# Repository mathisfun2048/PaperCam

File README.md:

# PaperCam: My Thought Process Behind This Project

## Description and Exigence

This is my third attempt at hardware design, and it's been so much fun!

The concept arose when I came across ads for disposable cameras for summer camps on YouTube. I remembered the nostalgia of taking instant pictures and the intrinsic joy they bring, but within the context of instant cameras being 1) expensive and 2) harmful to the environment. I want to bridge this gap by creating a digital camera that feels like an instant camera. 

The first thing I think of with instant photography is not knowing exactly how the picture is going to turn out; rather, just taking it and hoping for the best. That's why instead of opting for an LCD display, I chose an E-Ink display. Not only does it use significantly less power, but it can also show an instant snapshot *after* taking the picture, mimicking the feeling of instant photography. 

Another goal I had for this project was to intentionally keep things minimalistic. In a world where technology can have so many features, I wanted to create something simple with one purpose: taking a picture. There's this one Japanese brand (Muji!) that I have been enthralled with for the past 7 years, mainly due to their product's simplicity. Keeping this in mind, I was very mindful of which parts I needed to use. The only user inputs, really, are a power switch and a capture button, nothing excessive but enough to take a picture. Moreover, the e-ink display shows a glimpse of the photo after it has been taken, not necessarily the most detailed, but accurate enough to capture the likeness of whatever is being captured. I hope that this camera will encourage me to try to create memories instead of the best "picture" I hope this camera will let me be less preoccupied with how things look but rather will force me to capture things authentically. 

Here is everything I sourced. A identical version can be found in the BOM tab at the bottom of the README. 

NOTE: I know some items can be found cheaper through other retailars: the only problem is that my parents will only let me buy from the retailors below. If the cost goes above the allocated cost for my project, I will hapilly pay out of my own pocket. I am grateful to have the opportunity to build this, and I cannot do so if I don't buy the parts from the retailors below. 

| item                                       | quantity | cost   | source      | link                                                                                                                                                                                                             |
| ------------------------------------------ | -------- | ------ | ----------- | ---------------------------------------------------------------------------------------------------------------------------------------------------------------------------------------------------------------- |
| Raspberry Pi Zero 2 W                      | 1        | 14.99  | microcenter | [https://www.microcenter.com/product/643085/raspberry-pi-zero-2-w](https://www.microcenter.com/product/643085/raspberry-pi-zero-2-w)                                                                             |
| Camera                                     | 1        | 29.25  | adafruit    | [https://www.adafruit.com/product/5657](https://www.adafruit.com/product/5657)                                                                                                                                   |
| e-ink display                              | 1        | 34.99  | amazon      | [https://www.amazon.com/dp/B074NR1SW2](https://www.amazon.com/dp/B074NR1SW2)                                                                                                                                     |
| 64gb SD Card                               | 1        | 0      | myself      | n/a                                                                                                                                                                                                              |
| LiPo Batter 2200mAh                        | 1        | 9.95   | adafruit    | [https://www.adafruit.com/product/1781](https://www.adafruit.com/product/1781)                                                                                                                                   |
| powerboost 1000c                           | 1        | 19.95  | adafruit    | [https://www.adafruit.com/product/2465?srsltid=AfmBOop7pYqBCCEfueczVoFC1WawLn-4JDxrWe6MvBLNL__PzA9LbI22](https://www.adafruit.com/product/2465?srsltid=AfmBOop7pYqBCCEfueczVoFC1WawLn-4JDxrWe6MvBLNL__PzA9LbI22) |
| SPDT Switch                                | 1        | 0.95   | adafruit    | [https://www.adafruit.com/product/805](https://www.adafruit.com/product/805)                                                                                                                                     |
| 12mm Button                                | 1        | 5.95   | adafruit    | [https://www.adafruit.com/product/1010](https://www.adafruit.com/product/1010)                                                                                                                                   |
| Header for RPi                             | 1        | 1.75   | adafruit    | [https://www.adafruit.com/product/3907](https://www.adafruit.com/product/3907)                                                                                                                                   |
| 0.1uF Ceramic Capacitor                    | 2        | 1.95   | adafruit    | [https://www.adafruit.com/product/753](https://www.adafruit.com/product/753)                                                                                                                                     |
| 220uF Electrolytic Capacitor               | 1        | 2.95   | adafruit    | [https://www.adafruit.com/product/2192](https://www.adafruit.com/product/2192)                                                                                                                                   |
| Screws M2.5 × 6 mm \* 5, M2.5 x 10 mm \* 4 | 9        | 16.95  | adafruit    | [https://www.adafruit.com/product/3299](https://www.adafruit.com/product/3299)                                                                                                                                   |
| Custom PCB                                 | 1        | 8.6    | JCLPCB      | [https://jlcpcb.com](https://jlcpcb.com/)                                                                                                                                                                        |
| Total Cost                                 |          | ~148 |

## Schematic and PCB Design

I saw that with this project, spending all this time curating the BOM allowed my schematic and PCB design process to be significantly smoother. I was able to organically decide where components go such that the product can fulfill its purpose without having anything excess. I feel this starked my approach in my Hackpad design, where I flooded the PCB with an LED matrix, OLED, and encoder when perhaps the keys would have sufficed. The design of this project has been meditative, and I am grateful for that. One way I referenced this creative meditation in the design itself is through the inclusion of graphic design motifs I designed during the pandemic. The graphic design kept me sane then through its meditative nature, and I wanted to reference that simple creativity in the silkscreen. I will say that the silkscreen aesthetic starks the clean minimalistic nature of the CAD, and that is intentional: my graphic design motifs, in all their chaos, are a part of me and do not necessarily need to be advertised. To the user, I want the product to be simple elegant, and perfect for capturing memories. 

### Schematic

### PCB on Kicad

## Firmware

After I designed the PCB, I started on the firmware, the design of which garnered me the most personal growth. While I was able to exercise my research and design skills to a significantly larger extent in this project compared to Hackpad or Gamepad, the software designed for this is something I have never done before. I have never had multiple software files interact with each other in a product before. For instance, I started this project initially with just a runtime firmware, but then realized I needed to use shell too to initiate my code and the file structure and use the system to restart my Python code should it crash. I spent quite a bit coding, but I saw myself getting faster at it which amazed me. I started learning how to code maybe 2 years ago, and I am really proud of what I've been able to do here. 

Everything associated with the firmware can be found in the firmware directory. It has its own specialized README that explains what each file does. 

## CAD

After I was done with the code, I saved the hardest for last: CAD. I've never been good at CAD, but this project allowed me to show my style. When I did graphic design, I specialized in minimalistic designs which were meant to be abstract and aesthetically pleasing. I was highly influenced by the Bauhaus movement, and I am so glad I was able to incorporate that part of my personal style into this project. In keeping line with the "minimal" mindset, I wanted the design to be a simplified square Instax. That's why on the exterior form it almost looks like a kid's toy-- that is intentional. I don't want anything to distract from my camera being used to capture memories, even if it looks a tad blocky (I personally think it looks pretty cool). Making it look seamless on the outside was not easy, though. I utilized a top-case, bottom-case design where my PCB will screw into the bottom case before the top case is applied and the whole thing is screwed together. This required me to be able to hide my mounting screws inside the structure--the inside is much more chaotic than the clean exterior. For stability, I chose to indent the inside a tad so that the top case slides on and has a sense of rigidity. This is enhanced by the view-finder which acts as a "pole" holding everything together. I wanted my camera to not feel like something inherently precious, but rather something that can be taken places and used as a camera to capture memories. The only real adoration I have for it is the phrase "PaperCAM v1" on the user side of it. I want to remind myself that when I use this, it is something that I built and not something I simply bought. I want to remind myself that I have the agency to create things. 

Because everything is on a PCB this time, no fun illustrated wiring diagram :(. However, I did annotate the bellow images for y'all! 

## BOM

NOTE: I know some items can be found cheaper through other retailars: the only problem is that my parents will only let me buy from the retailors below. If the cost goes above teh allocated cost for my project, I will hapilly pay out of my own pocket. I am grateful to have the opportunity to build this, and I cannot do so if I don't buy the parts from the retailors below. 

| item                                       | quantity | cost   | source      | link                                                                                                                                                                                                             |
| ------------------------------------------ | -------- | ------ | ----------- | ---------------------------------------------------------------------------------------------------------------------------------------------------------------------------------------------------------------- |
| Raspberry Pi Zero 2 W                      | 1        | 14.99  | microcenter | [https://www.microcenter.com/product/643085/raspberry-pi-zero-2-w](https://www.microcenter.com/product/643085/raspberry-pi-zero-2-w)                                                                             |
| Camera                                     | 1        | 29.25  | adafruit    | [https://www.adafruit.com/product/5657](https://www.adafruit.com/product/5657)                                                                                                                                   |
| e-ink display                              | 1        | 34.99  | amazon      | [https://www.amazon.com/dp/B074NR1SW2](https://www.amazon.com/dp/B074NR1SW2)                                                                                                                                     |
| 64gb SD Card                               | 1        | 0      | myself      | n/a                                                                                                                                                                                                              |
| LiPo Batter 2200mAh                        | 1        | 9.95   | adafruit    | [https://www.adafruit.com/product/1781](https://www.adafruit.com/product/1781)                                                                                                                                   |
| powerboost 1000c                           | 1        | 19.95  | adafruit    | [https://www.adafruit.com/product/2465?srsltid=AfmBOop7pYqBCCEfueczVoFC1WawLn-4JDxrWe6MvBLNL__PzA9LbI22](https://www.adafruit.com/product/2465?srsltid=AfmBOop7pYqBCCEfueczVoFC1WawLn-4JDxrWe6MvBLNL__PzA9LbI22) |
| SPDT Switch                                | 1        | 0.95   | adafruit    | [https://www.adafruit.com/product/805](https://www.adafruit.com/product/805)                                                                                                                                     |
| 12mm Button                                | 1        | 5.95   | adafruit    | [https://www.adafruit.com/product/1010](https://www.adafruit.com/product/1010)                                                                                                                                   |
| Header for RPi                             | 1        | 1.75   | adafruit    | [https://www.adafruit.com/product/3907](https://www.adafruit.com/product/3907)                                                                                                                                   |
| 0.1uF Ceramic Capacitor                    | 2        | 1.95   | adafruit    | [https://www.adafruit.com/product/753](https://www.adafruit.com/product/753)                                                                                                                                     |
| 220uF Electrolytic Capacitor               | 1        | 2.95   | adafruit    | [https://www.adafruit.com/product/2192](https://www.adafruit.com/product/2192)                                                                                                                                   |
| Screws M2.5 × 6 mm \* 5, M2.5 x 10 mm \* 4 | 9        | 16.95  | adafruit    | [https://www.adafruit.com/product/3299](https://www.adafruit.com/product/3299)                                                                                                                                   |
| Custom PCB                                 | 1        | 8.6    | JCLPCB      | [https://jlcpcb.com](https://jlcpcb.com/)                                                                                                                                                                        |
| Total Cost                                 |          | ~148 |

## Parting Words

If you've made it so far, thank you. This project has been really personal for me, I don't know why. In the process, I've discovered more of what I value in design and feel that I have been able to refine my personal style. Because of this project, I think I finally feel confident with CAD. In the coding portions, I learned that I can be an actual DEV and not someone who just does practice problems for some test.

Hackclub and Highway, thank you so much for the opportunity to design and hopefully implement this project. 

Until next time,
Arya

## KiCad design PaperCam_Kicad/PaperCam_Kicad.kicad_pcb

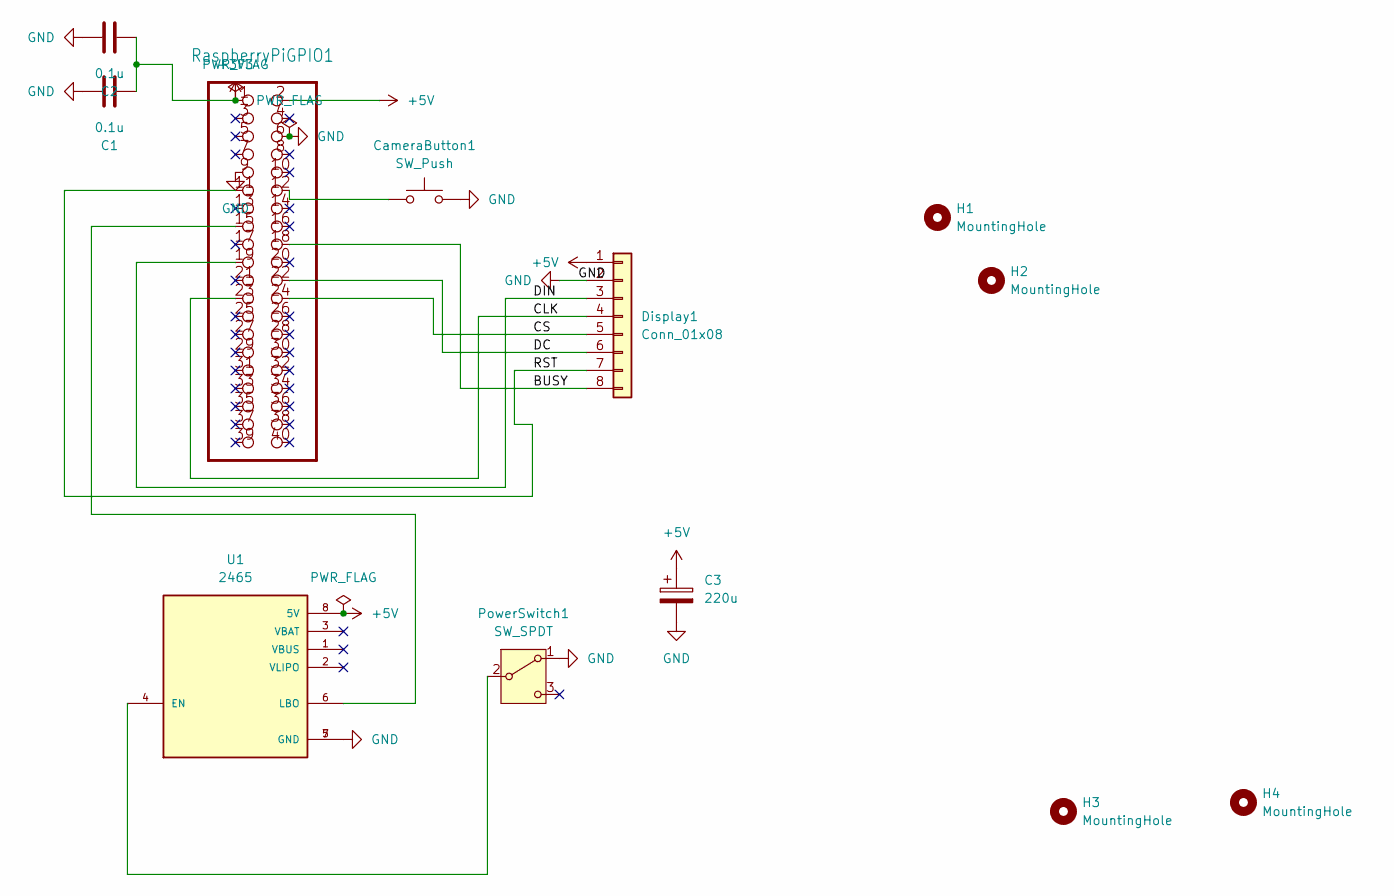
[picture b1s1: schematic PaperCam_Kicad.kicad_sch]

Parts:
C1, C2: 0.1u; C_Disc_D5.0mm_W2.5mm_P2.50mm
C3: 220u; CP_Radial_D5.0mm_P2.50mm
CameraButton1: SW_Push; SW_PUSH-12mm
Display1: Conn_01x08; PinHeader_1x08_P2.54mm_Vertical
H1, H2: MountingHole; MountingHole_2.7mm_M2.5
H3, H4: MountingHole; MountingHole_3mm
PowerSwitch1: SW_SPDT; SW_MINI-SPDT-SW
RaspberryPiGPIO1: Raspberry_Pi_Zero_Socketed_THT_FaceDown_MountingHoles
U1: 2465; MODULE_2465; PARTREV B

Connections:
+3V3: C1.1, C2.1, RaspberryPiGPIO1.1
+5V: C3.1, Display1.1, RaspberryPiGPIO1.2, U1.8 (5V)
/BUSY: Display1.8, RaspberryPiGPIO1.18
/CLK: Display1.4, RaspberryPiGPIO1.23
/CS: Display1.5, RaspberryPiGPIO1.24
/DC: Display1.6, RaspberryPiGPIO1.22
/DIN: Display1.3, RaspberryPiGPIO1.19
/RST: Display1.7, RaspberryPiGPIO1.11
GND: C1.2, C2.2, C3.2, CameraButton1.2, Display1.2, PowerSwitch1.1 (A), RaspberryPiGPIO1.6, RaspberryPiGPIO1.9, U1.5 (GND), U1.7 (GND)
unnamed: CameraButton1.1, RaspberryPiGPIO1.12
unnamed: PowerSwitch1.2 (B), U1.4 (EN)
unnamed: RaspberryPiGPIO1.15, U1.6 (LBO)

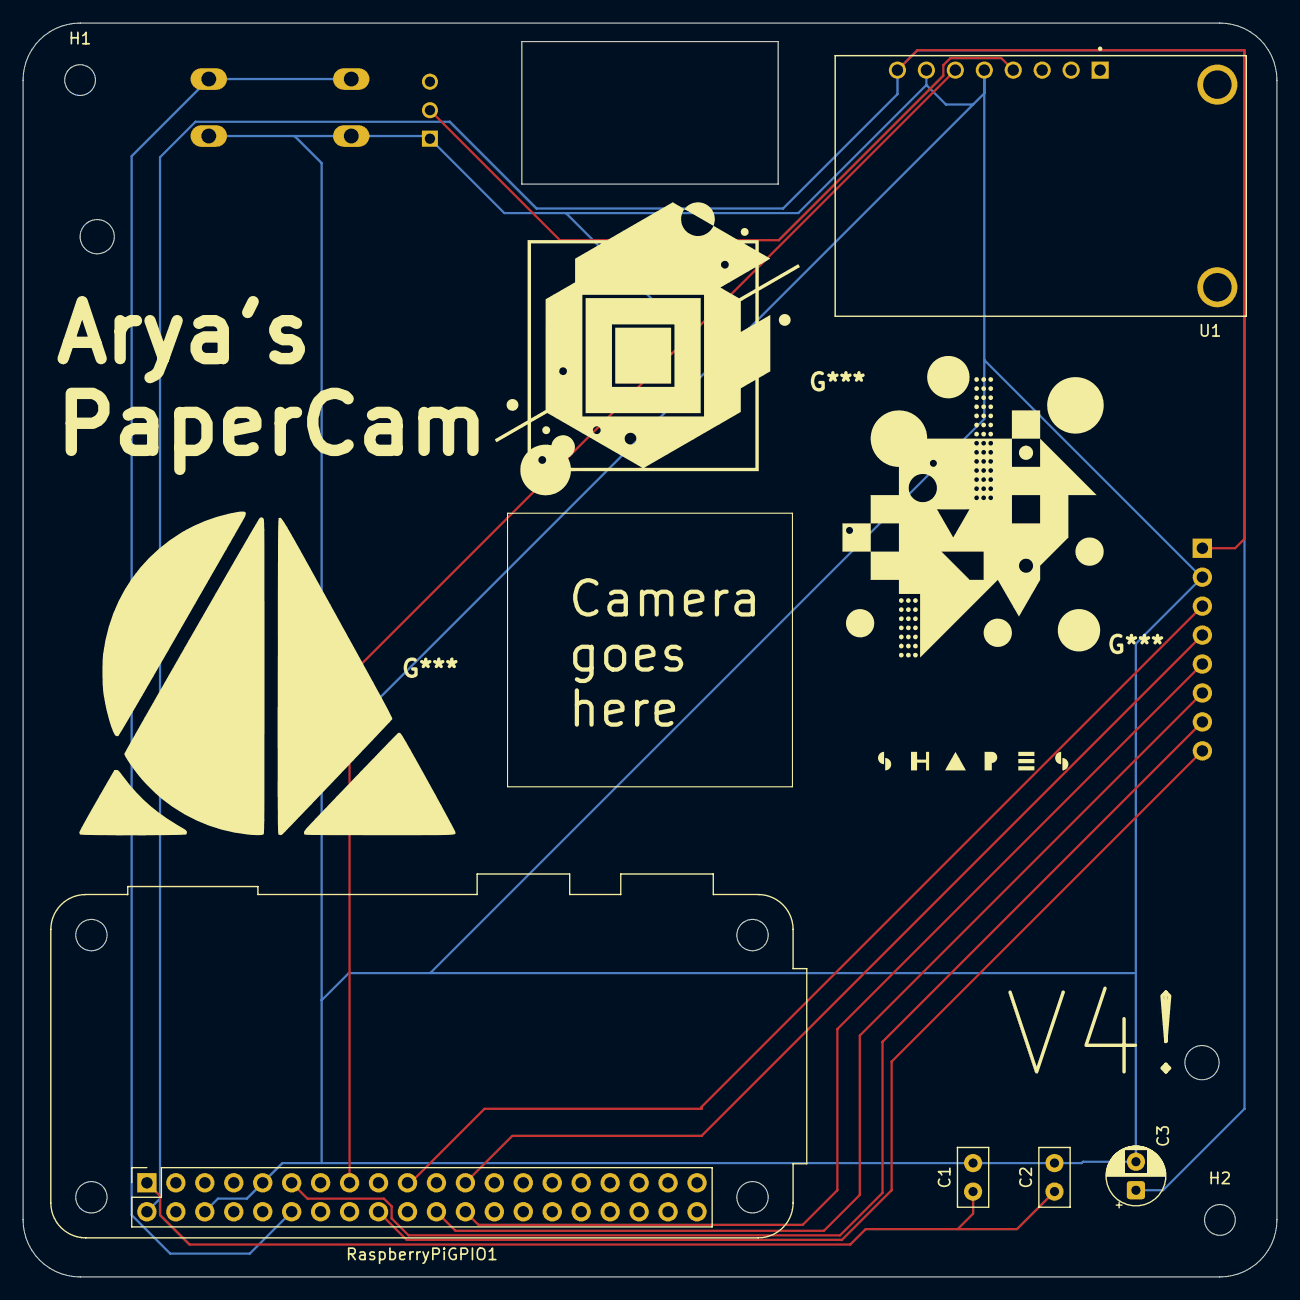
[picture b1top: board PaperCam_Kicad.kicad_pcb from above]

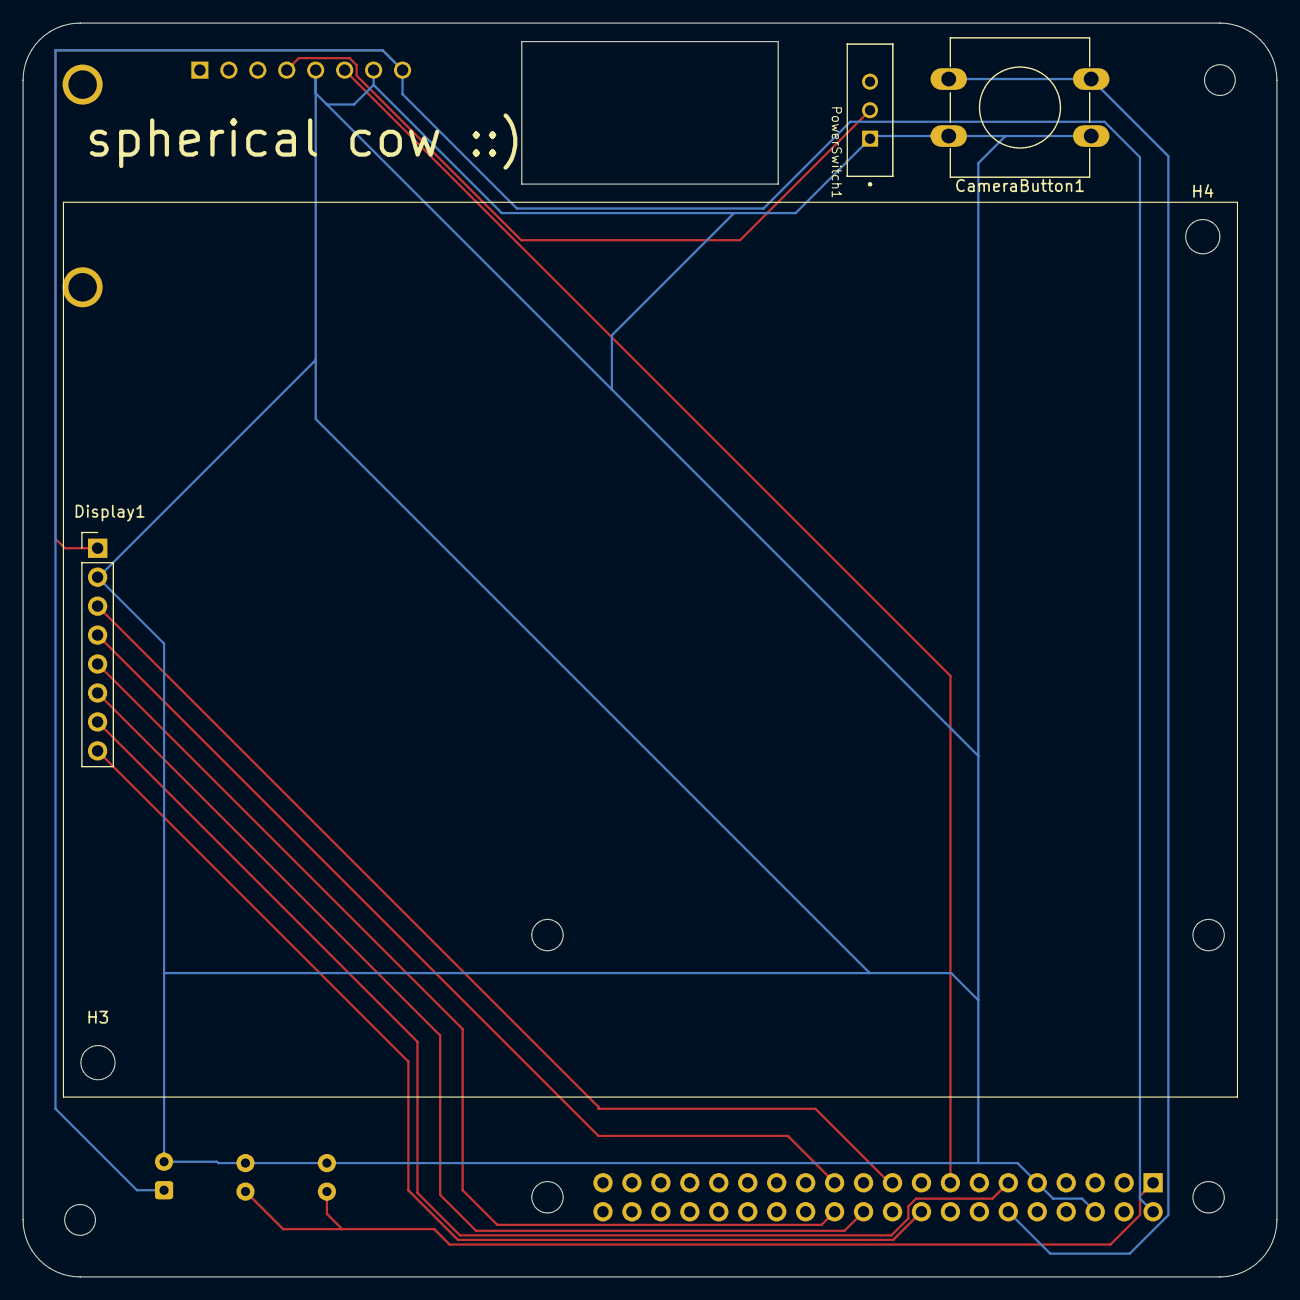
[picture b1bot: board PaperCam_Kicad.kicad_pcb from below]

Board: 2 copper layers, 110.0 x 110.0 mm, 12 parts (5 on the bottom side), 12 nets.

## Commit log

2025-06-25 added pcb files
2025-06-25 added software
2025-06-25 cad files
2025-06-25 added BOM and Gerbers
2025-06-25 added some stuff
2025-06-25 finishing touches
2025-06-26 Rename JOUNRAL.md to JOURNAL.md
2025-07-02 updated pcb design
2025-07-02 stuff
2025-07-02 fixed wiring
2025-07-02 fixed keyboard
